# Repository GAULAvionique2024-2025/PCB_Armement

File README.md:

# PCB_Armement
Le pcb d'armement et de gestion d'alimentation pour le projet de Launch Canada 2025

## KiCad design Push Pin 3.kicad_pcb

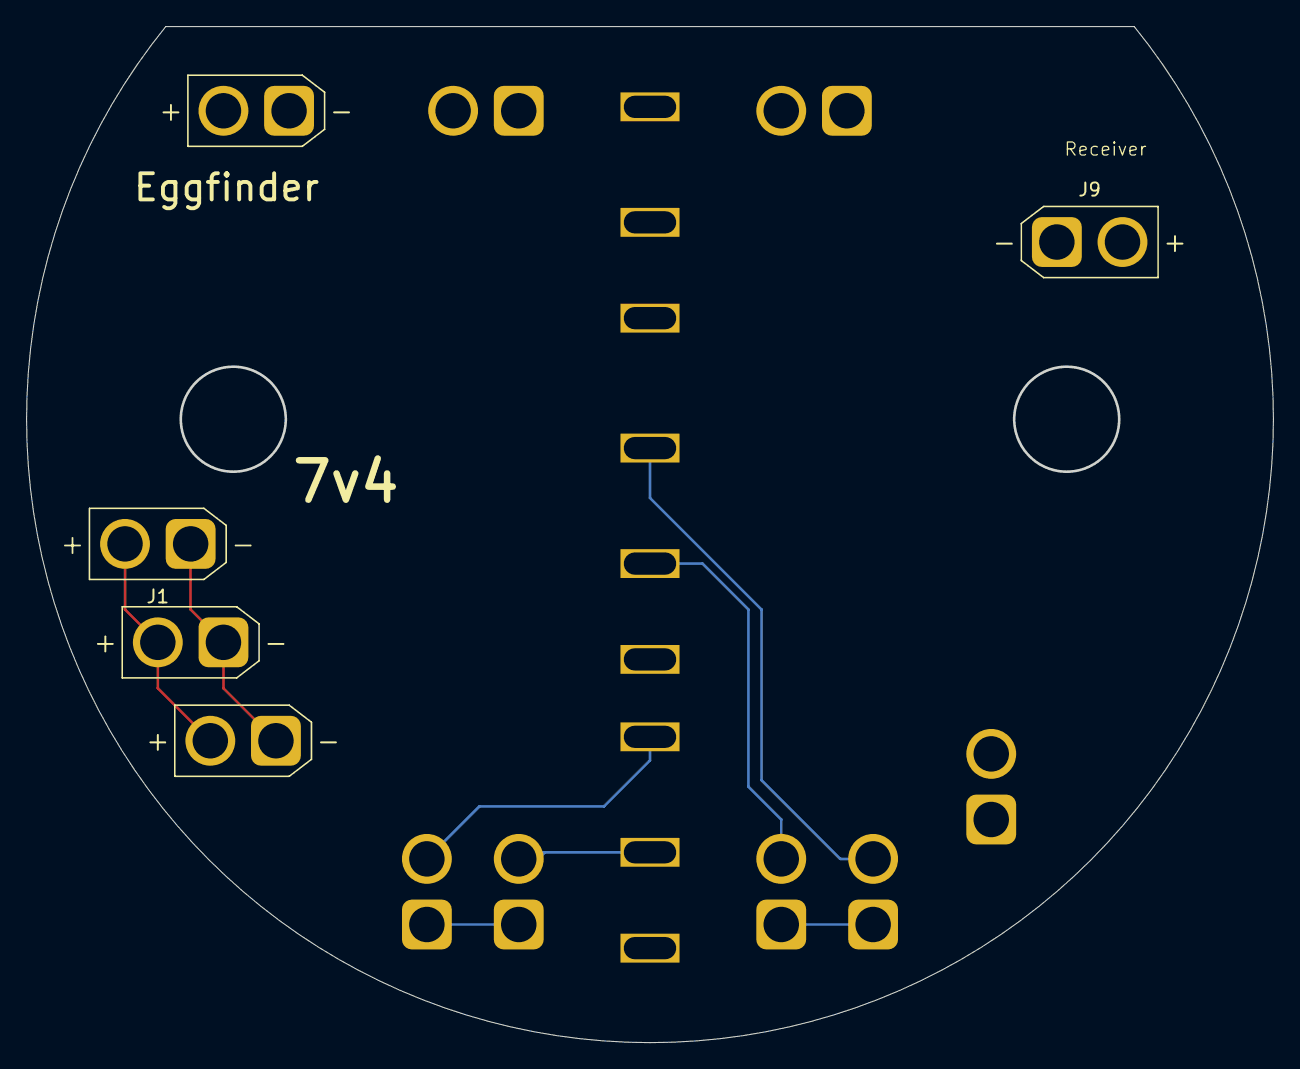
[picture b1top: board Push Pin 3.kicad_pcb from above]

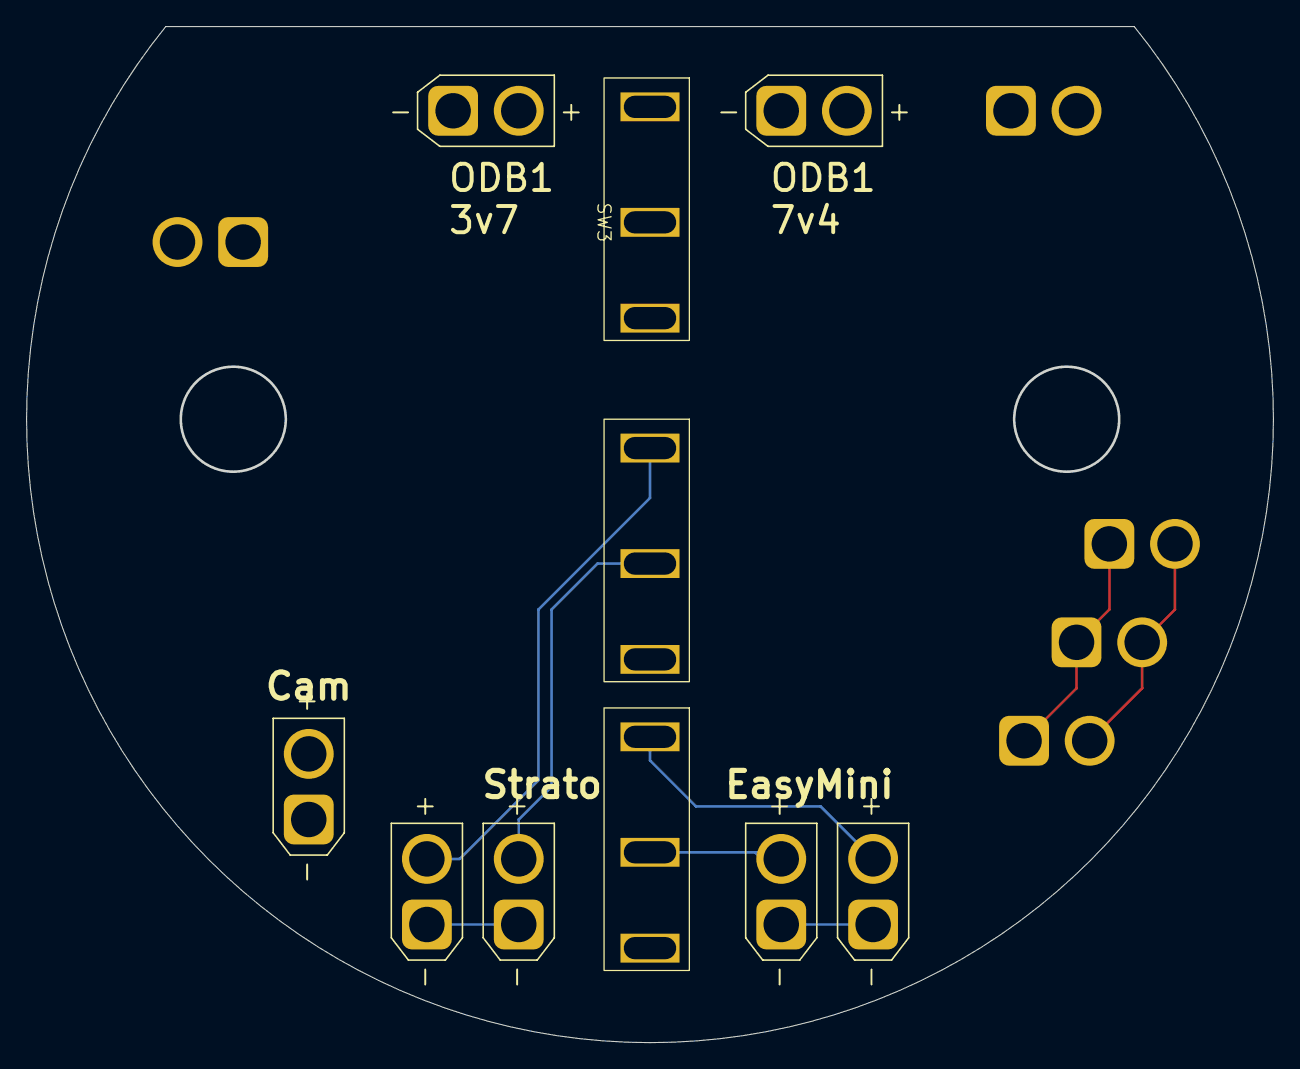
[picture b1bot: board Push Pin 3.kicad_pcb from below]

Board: 2 copper layers, 95.0 x 77.4 mm, 15 parts (10 on the bottom side), 9 nets.

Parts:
J1, J2, J3, J4, J5, J6, J7, J8, J9, J10, J11, J12: Screw_Terminal_01x02; AMASS_XT30U-M_1x02_P5.0mm_Vertical
SW1, SW2, SW3: SW_DPDT_x2; Omrun_SS-01GL13

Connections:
unnamed: J1.2, J2.2, J3.2, SW3.2 (B)
unnamed: J4.1, J5.1
unnamed: J4.2, SW2.2 (B)
unnamed: J5.2, SW2.1 (A)
unnamed: J6.1, J7.1
unnamed: J6.2, SW1.2 (B)
unnamed: J7.2, SW1.1 (A)
V+: J8.1, J9.1, J10.1, J11.1, SW3.3 (C)
V-: J1.1, J2.1, J3.1, J8.2, J9.2, J10.2, J11.2, J12.2

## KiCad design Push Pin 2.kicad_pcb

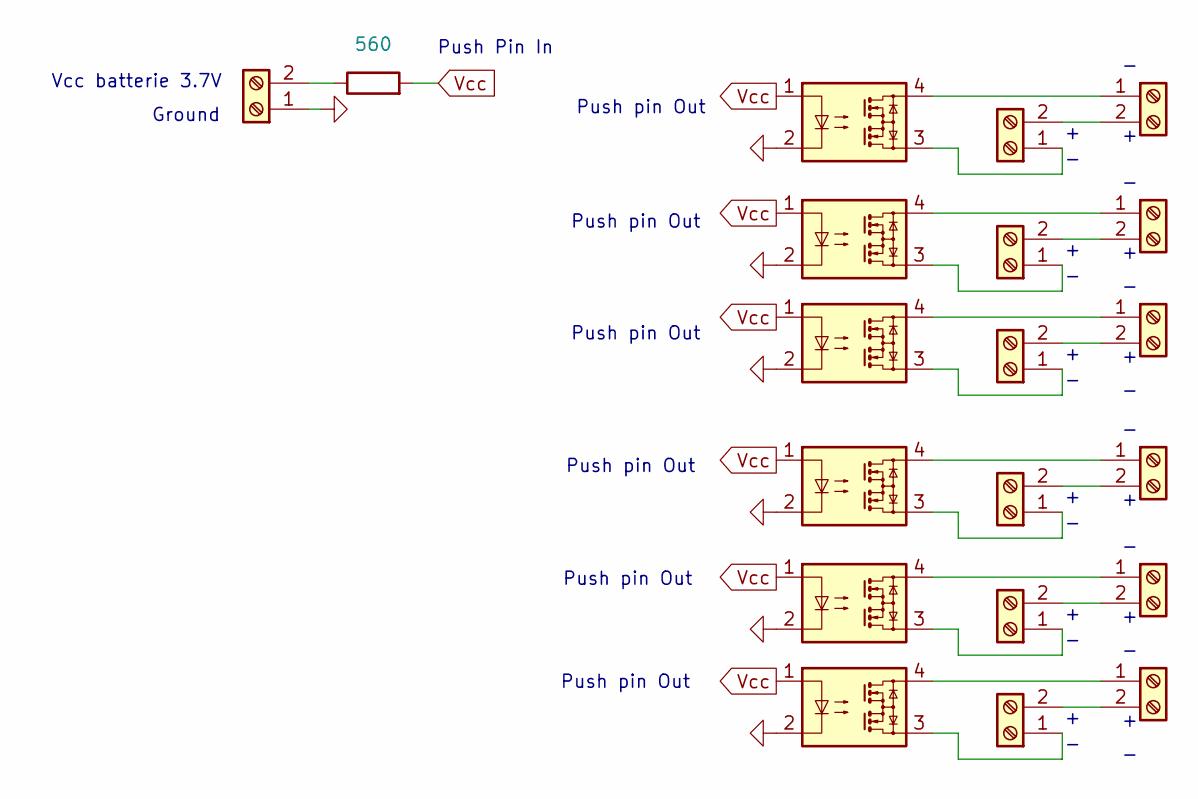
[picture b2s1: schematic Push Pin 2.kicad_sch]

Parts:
J1, J4, J5, J6, J7, J8, J9, J10, J11, J12, J13: Screw_Terminal_01x02; AMASS_XT30U-M_1x02_P5.0mm_Vertical; LCSC Part # C129184
J2, J3: Screw_Terminal_01x02; AMASS_XT60-F_1x02_P7.20mm_Vertical; LCSC Part # C129184
R1: 560; R_0805_2012Metric
U1, U2, U3, U4, U5, U6: CPC1017N; SOP-4_3.8x4.1mm_P2.54mm; LCSC Part # C2760365

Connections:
GND: J1.1, U1.2, U2.2, U3.2, U4.2, U5.2, U6.2
unnamed: J1.2, R1.1
unnamed: J2.1, U1.3
unnamed: J2.2, J3.2
unnamed: J3.1, U1.4
unnamed: J4.1, U2.3
unnamed: J4.2, J5.2
unnamed: J5.1, U2.4
unnamed: J6.1, U3.3
unnamed: J6.2, J7.2
unnamed: J7.1, U3.4
unnamed: J8.1, U4.3
unnamed: J9.1, U5.3
unnamed: J10.1, U6.3
unnamed: J10.2, J13.2
unnamed: J11.1, U4.4
unnamed: J8.2, J11.2
unnamed: J12.1, U5.4
unnamed: J9.2, J12.2
unnamed: J13.1, U6.4
Vcc: R1.2, U1.1, U2.1, U3.1, U4.1, U5.1, U6.1

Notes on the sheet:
Vcc batterie 3.7V
Push pin Out
Push Pin In
Ground

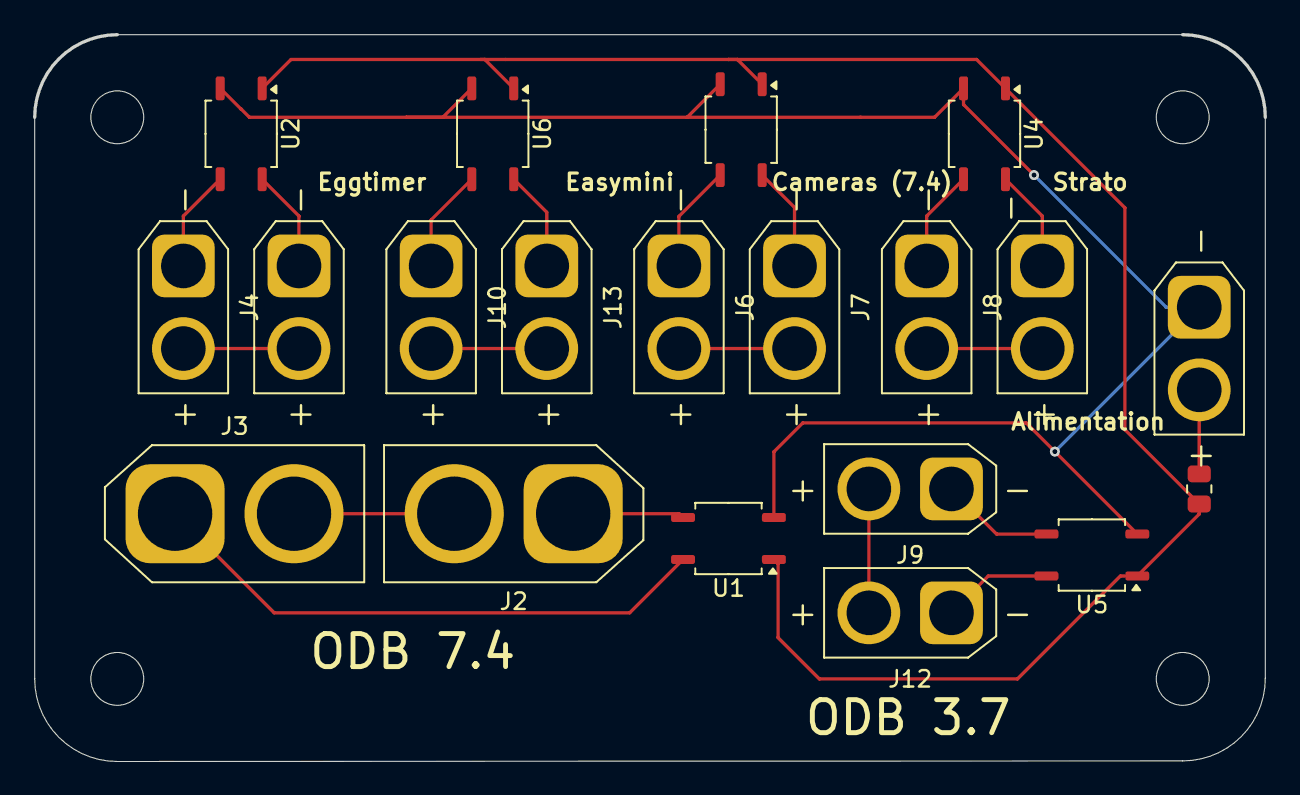
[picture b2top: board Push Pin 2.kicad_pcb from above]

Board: 2 copper layers, 74.5 x 44.0 mm, 20 parts (0 on the bottom side), 21 nets.
